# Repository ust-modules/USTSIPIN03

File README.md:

## USTSIPIN03 - Semiconductor-based ionizing radiation dosimeter and spectrometer analog front-end

The USTSIPIN03 is developed as a single-board improved variant of the [PIND02](https://github.com/mlab-modules/PIND02) and [PCRD07](https://github.com/mlab-modules/PCRD07) modules from the [MLAB.cz development system](https://www.mlab.cz/). The analog front-end is the sensing component of the [AIRDOS04 cosmic radiation detector and dosimeter](https://docs.dos.ust.cz/airdos/AIRDOS04).

### Features

* High-sensitivity silicon semiconductor PIN diode detector front-end
* Low-noise analog signal chain optimized for wide-energy radiation detection
* Designed for spectrometric and dosimetric measurements
* Suitable for connection to system MCU or FPGA via SPI interface
* Auxiliary I2C interface for service and calibration data access

### Electrical and Interface Specifications

* **Power supply**: +5 V DC
* **Maximum power consumption**: 5.5 mA (28 mW)
* **Main data interface**: SPI with up to 15 MHz system clock
* **Service interface**: I2C with access to
    * Temperature and humidity sensors
    * Unique serial number
    * Calibration memory
* Dimensions: 70.65 x 50.3 x 10 mm
* Mass: 24 g (including connector) 

### Measurement Specifications

* **Detection element**: Silicon PIN diode, volume 44 mm³
* **Effective number of energy channels**: ~65000
* **Deposited energy range**: 40 keV to 80 MeV
* **Spectral resolution**: 15 ±2 keV
* **Maximum sampling rate**: 250 kHz
* **Measurement modes**:
  * Pulse counting
  * Deposited energy spectroscopy
  * Dose rate estimation

### Applications

* Cosmic ray detection
* Environmental radiation monitoring
* Portable dosimetry systems
* Radiation protection systems
  
### Related Projects

* [AIRDOS04](https://github.com/UniversalScientificTechnologies/AIRDOS04) - Complete radiation detection system based on USTSIPIN03
* [PIND02](https://github.com/mlab-modules/PIND02) - Predecessor MLAB module
* [PCRD07](https://github.com/mlab-modules/PCRD07) - Related MLAB analog front-end module

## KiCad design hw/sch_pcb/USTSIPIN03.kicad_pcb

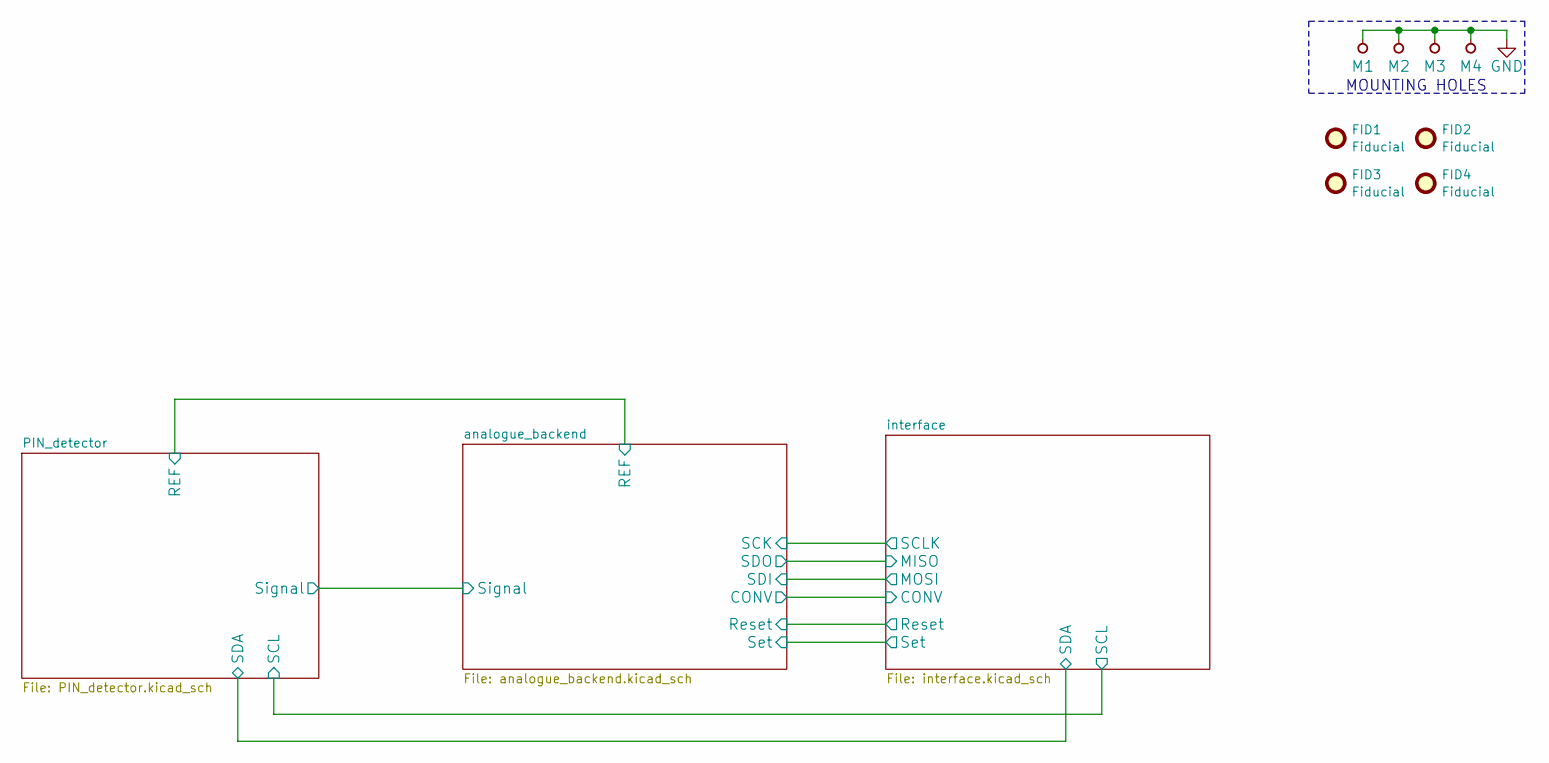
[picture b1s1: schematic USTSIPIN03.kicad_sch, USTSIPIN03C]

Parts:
FID1, FID2, FID3, FID4: Fiducial; Fiducial_1mm_Mask2mm
M1, M2, M3, M4: HOLE; MountingHole_3mm

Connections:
GND: M1.1, M2.1, M3.1, M4.1; also elsewhere on the board

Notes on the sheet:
MOUNTING HOLES

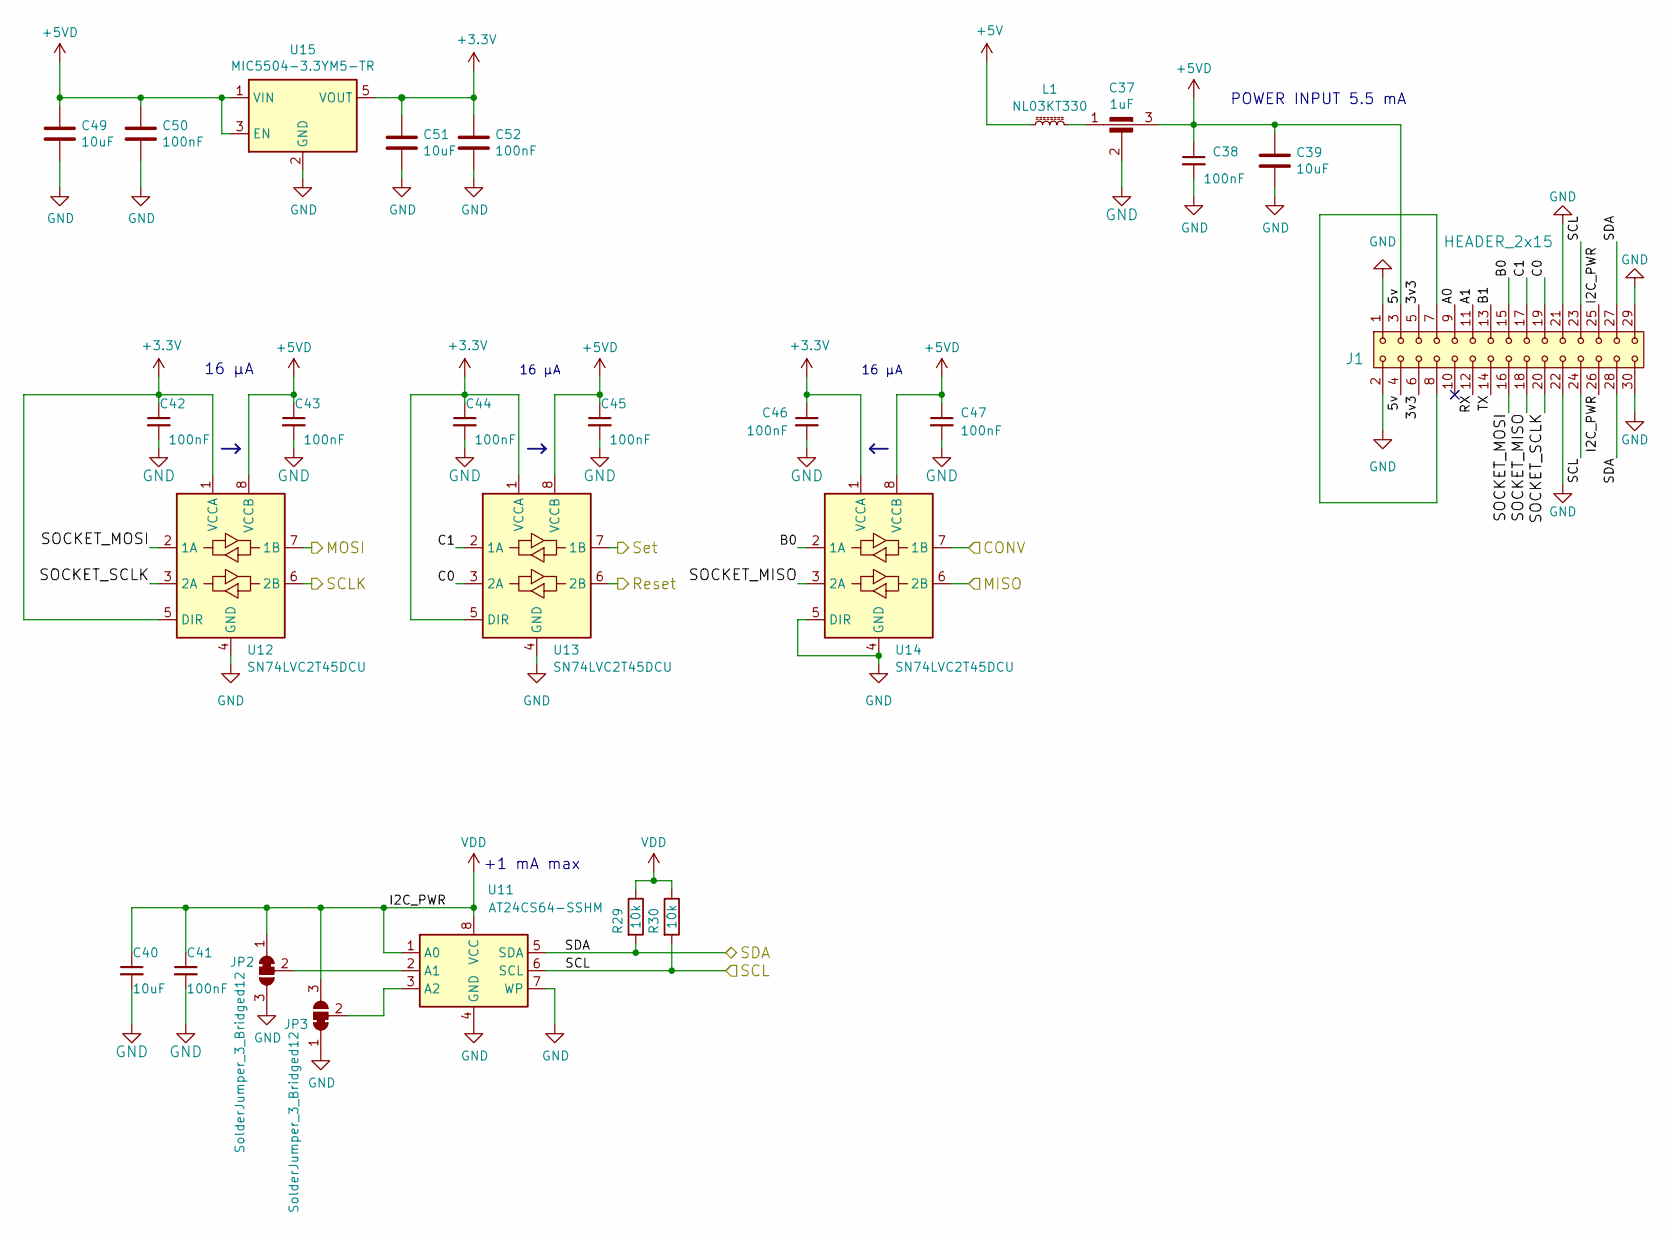
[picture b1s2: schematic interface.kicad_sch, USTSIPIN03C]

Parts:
C37: 1uF; FIR_0805
C38, C41, C42, C43, C44, C45, C46, C47, C50, C52: 100nF; C_0805_2012Metric
C39, C40, C49, C51: 10uF; C_0805_2012Metric
J1: HEADER_2x15; Straight_2x15
JP2, JP3: SolderJumper_3_Bridged12; SolderJumper-3_P1.3mm_Bridged12_RoundedPad1.0x1.5mm
L1: NL03KT330; L_0603_1608Metric_Pad1.05x0.95mm_HandSolder
R29, R30: 10k; R_0805_2012Metric
U11: AT24CS64-SSHM; SOIC-8_3.9x4.9mm_P1.27mm
U12, U13, U14: SN74LVC2T45DCU; VSSOP-8_2.3x2mm_P0.5mm
U15: MIC5504-3.3YM5-TR; SOT-23-5

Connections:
+3.3V: C42.1, C44.1, C46.1, C51.1, C52.1, U12.1 (VCCA), U12.5 (DIR), U13.1 (VCCA), U13.5 (DIR), U14.1 (VCCA), U15.5 (VOUT)
+5V: L1.1; also elsewhere on the board
+5VD: C37.3, C38.1, C39.1, C43.1, C45.1, C47.1, C49.1, C50.1, J1.3, J1.4, U12.8 (VCCB), U13.8 (VCCB), U14.8 (VCCB), U15.1 (VIN), U15.3 (EN); also elsewhere on the board
/analogue_backend/CONV: U14.7 (1B); also elsewhere on the board
/analogue_backend/Reset: U13.6 (2B); also elsewhere on the board
/analogue_backend/SCK: U12.6 (2B); also elsewhere on the board
/analogue_backend/SDI: U12.7 (1B); also elsewhere on the board
/analogue_backend/SDO: U14.6 (2B); also elsewhere on the board
/analogue_backend/Set: U13.7 (1B); also elsewhere on the board
/interface/3v3: J1.5, J1.6
/interface/A0: J1.9
/interface/A1: J1.11
/interface/B0: J1.15, U14.2 (1A)
/interface/B1: J1.13
/interface/C0: J1.19, U13.3 (2A)
/interface/C1: J1.17, U13.2 (1A)
/interface/RX: J1.12
/interface/SCL: J1.23, J1.24, R30.2, U11.6 (SCL); also elsewhere on the board
/interface/SDA: J1.27, J1.28, R29.2, U11.5 (SDA); also elsewhere on the board
/interface/SOCKET_MISO: J1.18, U14.3 (2A)
/interface/SOCKET_MOSI: J1.16, U12.2 (1A)
/interface/SOCKET_SCLK: J1.20, U12.3 (2A)
/interface/TX: J1.14
GND: C37.2, C38.2, C39.2, C40.2, C41.2, C42.2, C43.2, C44.2, C45.2, C46.2, C47.2, C49.2, C50.2, C51.2, C52.2, J1.1, J1.2, J1.21, J1.22, J1.29, J1.30, JP2.3 (B), JP3.1 (A), U11.4 (GND), U11.7 (WP), U12.4 (GND), U13.4 (GND), U14.4 (GND), U14.5 (DIR), U15.2 (GND); also elsewhere on the board
unnamed: C37.1, L1.2
unnamed: J1.7, J1.8
unnamed: JP2.2 (C), U11.2 (A1)
unnamed: JP3.2 (C), U11.3 (A2)
VDD: C40.1, C41.1, J1.25, J1.26, JP2.1 (A), JP3.3 (B), R29.1, R30.1, U11.1 (A0), U11.8 (VCC); also elsewhere on the board

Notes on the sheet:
+1 mA max
16 μA
POWER INPUT 5.5 mA

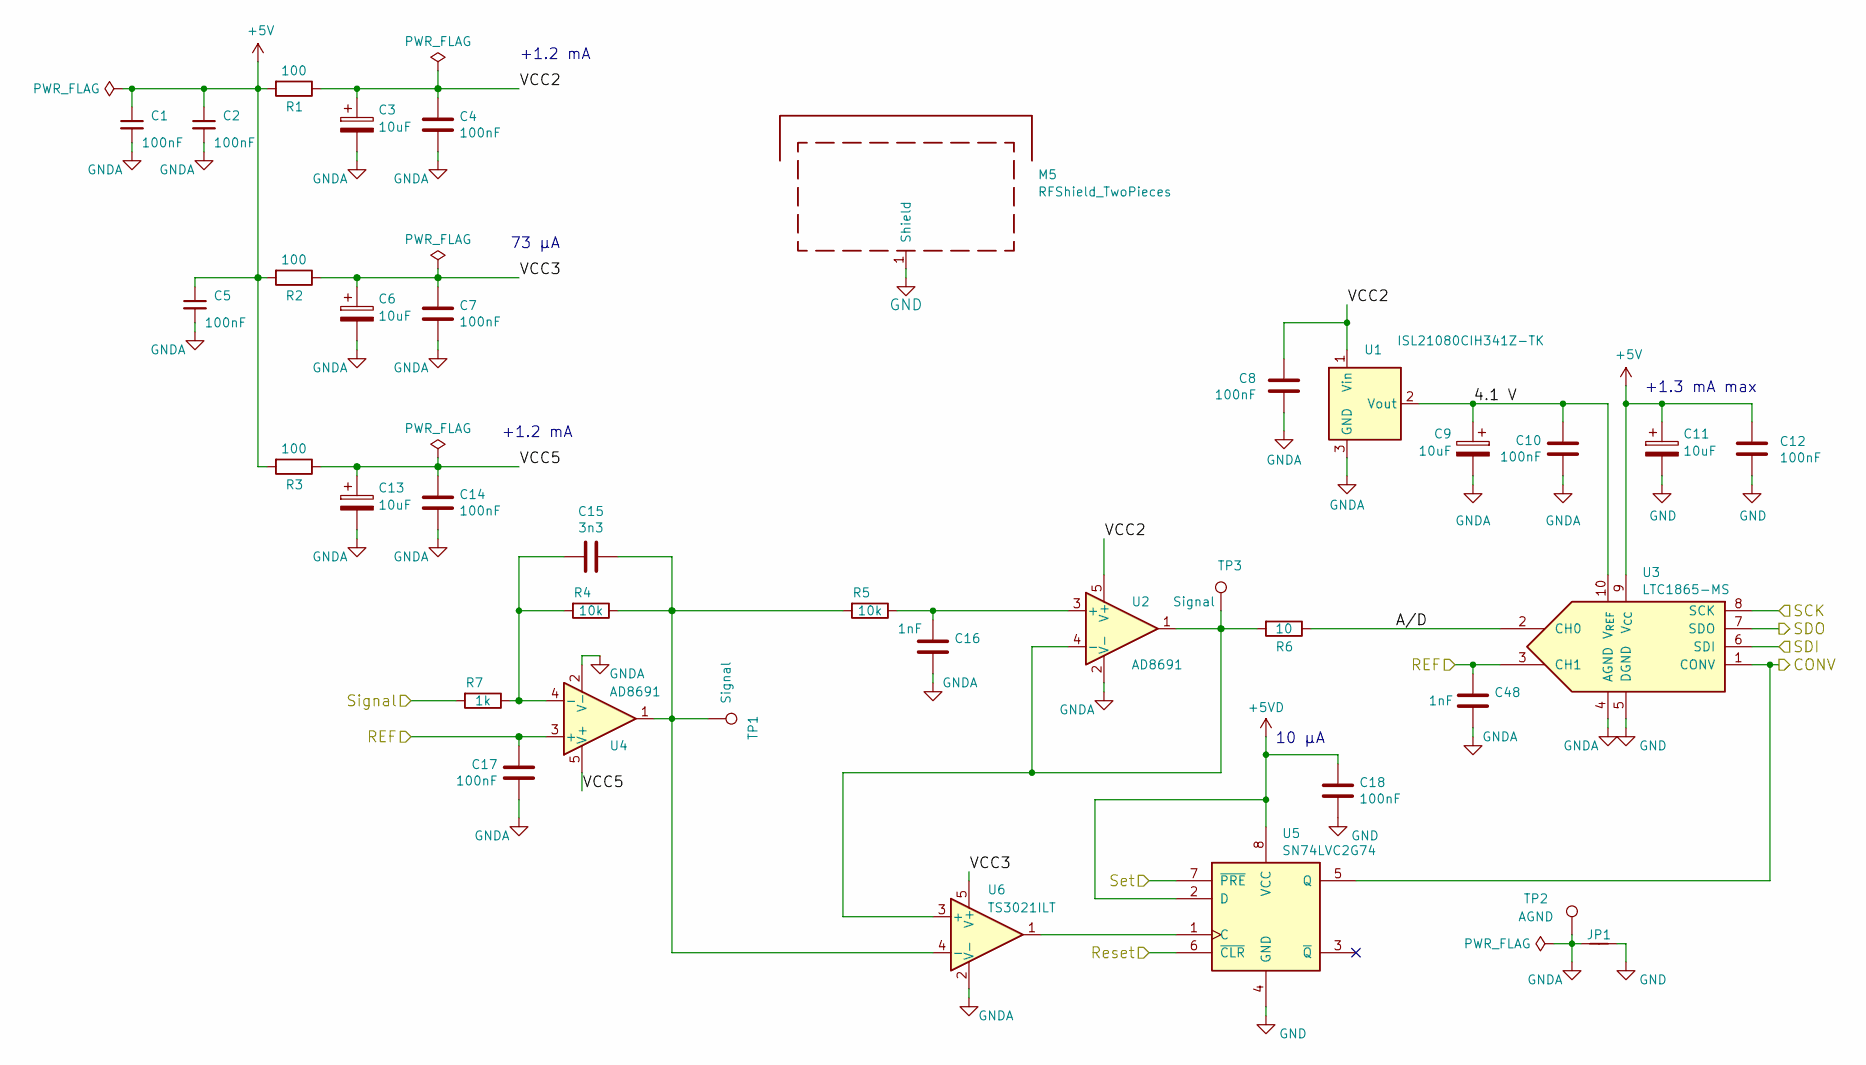
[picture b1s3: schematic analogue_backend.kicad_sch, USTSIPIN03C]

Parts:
C1, C2, C4, C5, C7, C8, C10, C12, C14, C17, C18: 100nF; C_0805_2012Metric
C3, C6, C9, C11, C13: 10uF; CP_EIA-3216-18_Kemet-A
C15: 3n3; C_0805_2012Metric
C16, C48: 1nF; C_0805_2012Metric
JP1: Jumper_2_Bridged; NetTie-2_SMD_Pad0.5mm
M5: RFShield_TwoPieces; Laird_Technologies_BMI-S-210-F_44.00x30.50mm
R1, R2, R3: 100; R_0805_2012Metric
R4, R5: 10k; R_0805_2012Metric
R6: 10; R_0805_2012Metric
R7: 1k; R_0805_2012Metric
TP1, TP3: Signal; TestPoint_Pad_D1.0mm
TP2: AGND; TestPoint_Pad_D1.0mm
U1: ISL21080CIH341Z-TK; SOT-23
U2, U4: AD8691; TSOT-23-5
U3: LTC1865-MS; MSOP-10_3x3mm_P0.5mm
U5: SN74LVC2G74; VSSOP-8_2.3x2mm_P0.5mm
U6: TS3021ILT; SOT-23-5

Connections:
+5V: C1.1, C2.1, C5.1, C11.1, C12.1, R1.2, R2.2, R3.2, U3.9 (V_{CC}); also elsewhere on the board
+5VD: C18.1, U5.2 (D), U5.8 (VCC); also elsewhere on the board
/PIN_detector/REF: C17.1, C48.1, U3.3 (CH1), U4.3 (+); also elsewhere on the board
/PIN_detector/Signal: R7.2; also elsewhere on the board
/analogue_backend/4.1 V: C9.1, C10.1, U1.2 (Vout), U3.10 (V_{REF})
/analogue_backend/A/D: R6.1, U3.2 (CH0)
/analogue_backend/CONV: U3.1 (CONV), U5.5 (Q); also elsewhere on the board
/analogue_backend/Reset: U5.6 (~CLR); also elsewhere on the board
/analogue_backend/SCK: U3.8 (SCK); also elsewhere on the board
/analogue_backend/SDI: U3.6 (SDI); also elsewhere on the board
/analogue_backend/SDO: U3.7 (SDO); also elsewhere on the board
/analogue_backend/Set: U5.7 (~PRE); also elsewhere on the board
/analogue_backend/VCC2: C3.1, C4.1, C8.1, R1.1, U1.1 (Vin), U2.5 (V+)
/analogue_backend/VCC3: C6.1, C7.1, R2.1, U6.5 (V+)
/analogue_backend/VCC5: C13.1, C14.1, R3.1, U4.5 (V+)
GND: C11.2, C12.2, C18.2, JP1.2, M5.1 (Shield), U3.5 (DGND), U5.4 (GND); also elsewhere on the board
GNDA: C1.2, C2.2, C3.2, C4.2, C5.2, C6.2, C7.2, C8.2, C9.2, C10.2, C13.2, C14.2, C16.2, C17.2, C48.2, JP1.1, TP2.1, U1.3 (GND), U2.2 (V-), U3.4 (AGND), U4.2 (V-), U6.2 (V-); also elsewhere on the board
unnamed: C16.1, R5.1, U2.3 (+)
unnamed: R6.2, TP3.1, U2.1, U2.4 (-), U6.3 (+)
unnamed: C15.2, R4.2, R7.1, U4.4 (-)
unnamed: U5.1 (C), U6.1
unnamed: C15.1, R4.1, R5.2, TP1.1, U4.1, U6.4 (-)

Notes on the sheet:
+1.3 mA max
+1.2 mA
73 μA
10 μA

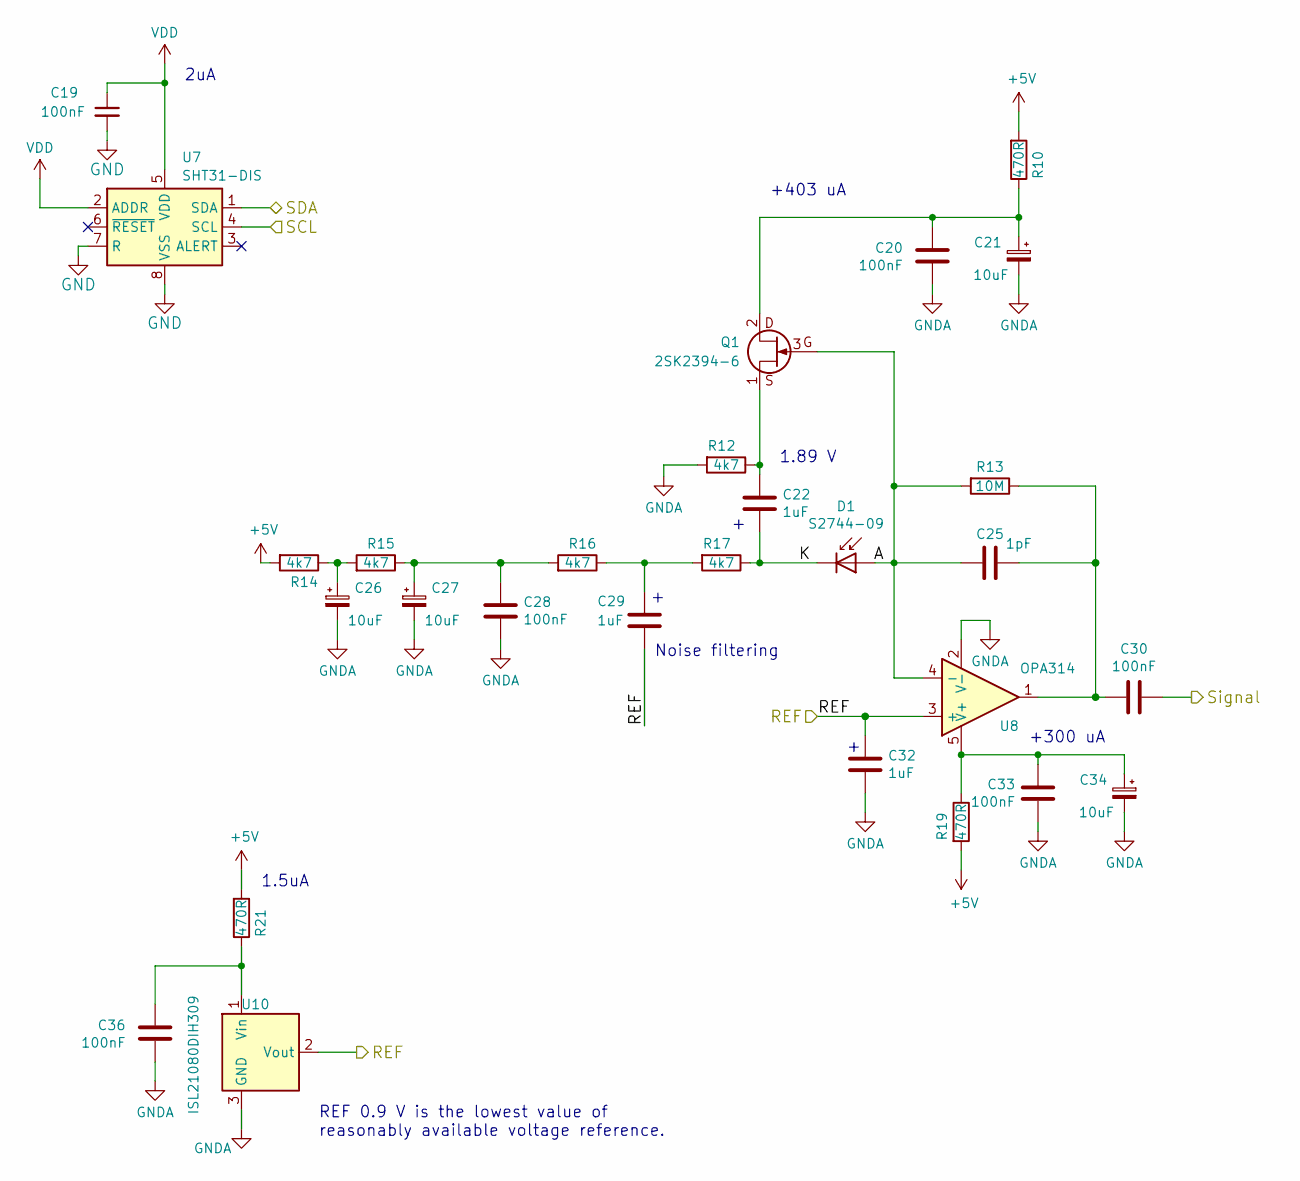
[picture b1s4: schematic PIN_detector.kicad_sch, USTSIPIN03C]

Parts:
C19, C20, C28, C30, C33, C36: 100nF; C_0805_2012Metric
C21, C26, C27, C34: 10uF; CP_EIA-3216-18_Kemet-A
C22, C29, C32: 1uF; C_1210_3225Metric
C25: 1pF; C_0805_2012Metric
D1: S2744-09; HAMAMATSU_S2744-09
Q1: 2SK2394-6; SOT-23
R10, R19, R21: 470R; R_0805_2012Metric
R12, R14, R15, R16, R17: 4k7; R_0805_2012Metric
R13: 10M; R_0805_2012Metric
U7: SHT31-DIS; Sensirion_DFN-8-1EP_2.5x2.5mm_P0.5mm_EP1.1x1.7mm
U8: OPA314; SOT-23-5
U10: ISL21080DIH309; SOT-23

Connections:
+5V: R10.2, R14.2, R19.2, R21.2; also elsewhere on the board
/PIN_detector/A: C25.2, D1.2 (A), Q1.3 (G), R13.2, U8.4 (-)
/PIN_detector/K: C22.2, D1.1 (K), R17.1
/PIN_detector/REF: C29.2, C32.1, U8.3 (+), U10.2 (Vout); also elsewhere on the board
/PIN_detector/Signal: C30.1; also elsewhere on the board
/interface/SCL: U7.4 (SCL); also elsewhere on the board
/interface/SDA: U7.1 (SDA); also elsewhere on the board
GND: C19.2, U7.7 (R), U7.8 (VSS), U7.9 (VSS); also elsewhere on the board
GNDA: C20.2, C21.2, C26.2, C27.2, C28.2, C32.2, C33.2, C34.2, C36.2, R12.2, U8.2 (V-), U10.3 (GND); also elsewhere on the board
unnamed: C25.1, C30.2, R13.1, U8.1
unnamed: C26.1, R14.1, R15.2
unnamed: C27.1, C28.1, R15.1, R16.2
unnamed: C29.1, R16.1, R17.2
unnamed: C20.1, C21.1, Q1.2 (D), R10.1
unnamed: C22.1, Q1.1 (S), R12.1
unnamed: C33.1, C34.1, R19.1, U8.5 (V+)
unnamed: C36.1, R21.1, U10.1 (Vin)
VDD: C19.1, U7.2 (ADDR), U7.5 (VDD); also elsewhere on the board

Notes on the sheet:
1.89 V
2uA
Noise filtering
REF 0.9 V is the lowest value of reasonably available voltage reference.
1.5uA
+300 uA
+403 uA

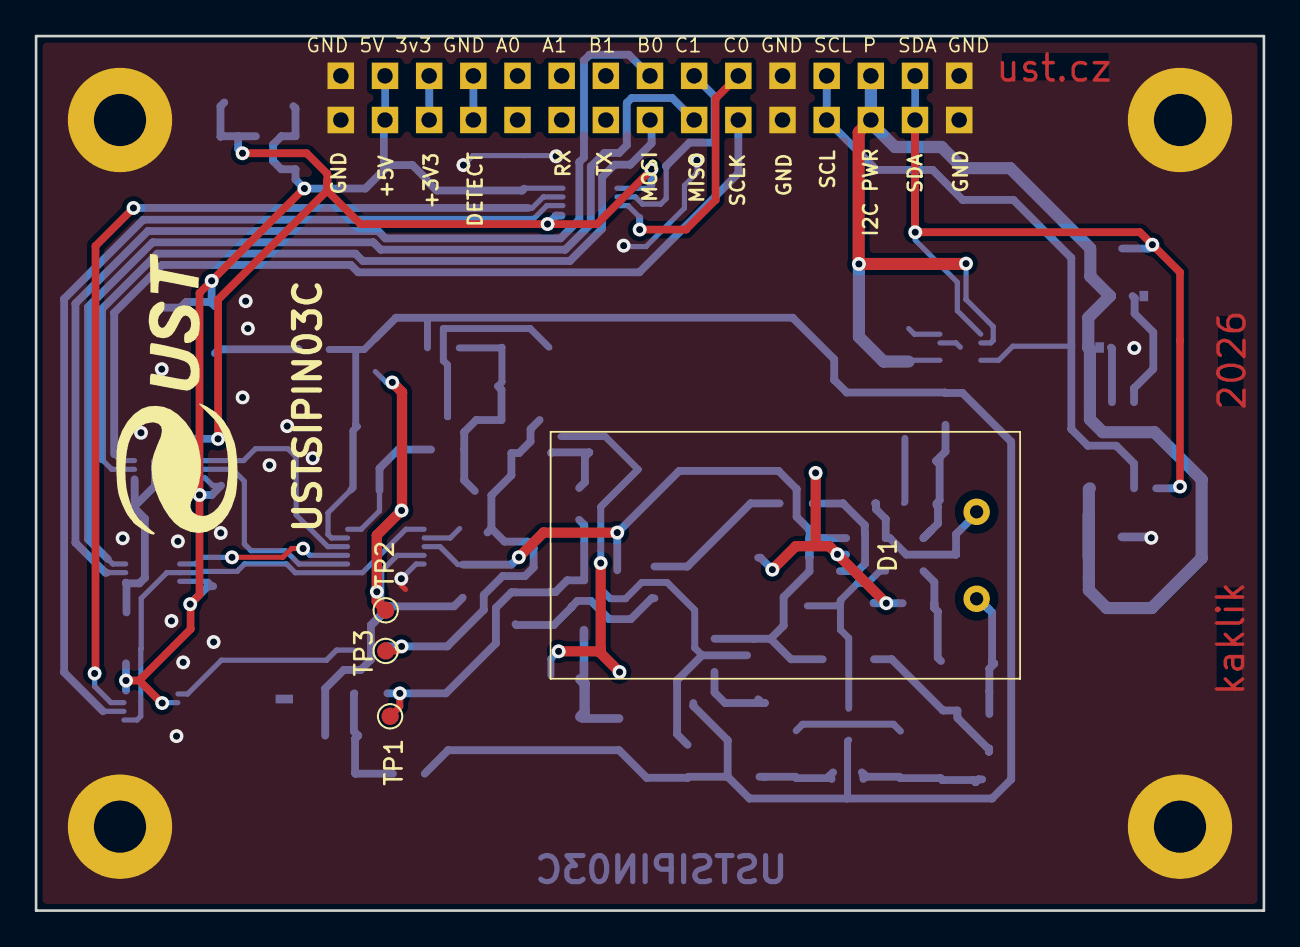
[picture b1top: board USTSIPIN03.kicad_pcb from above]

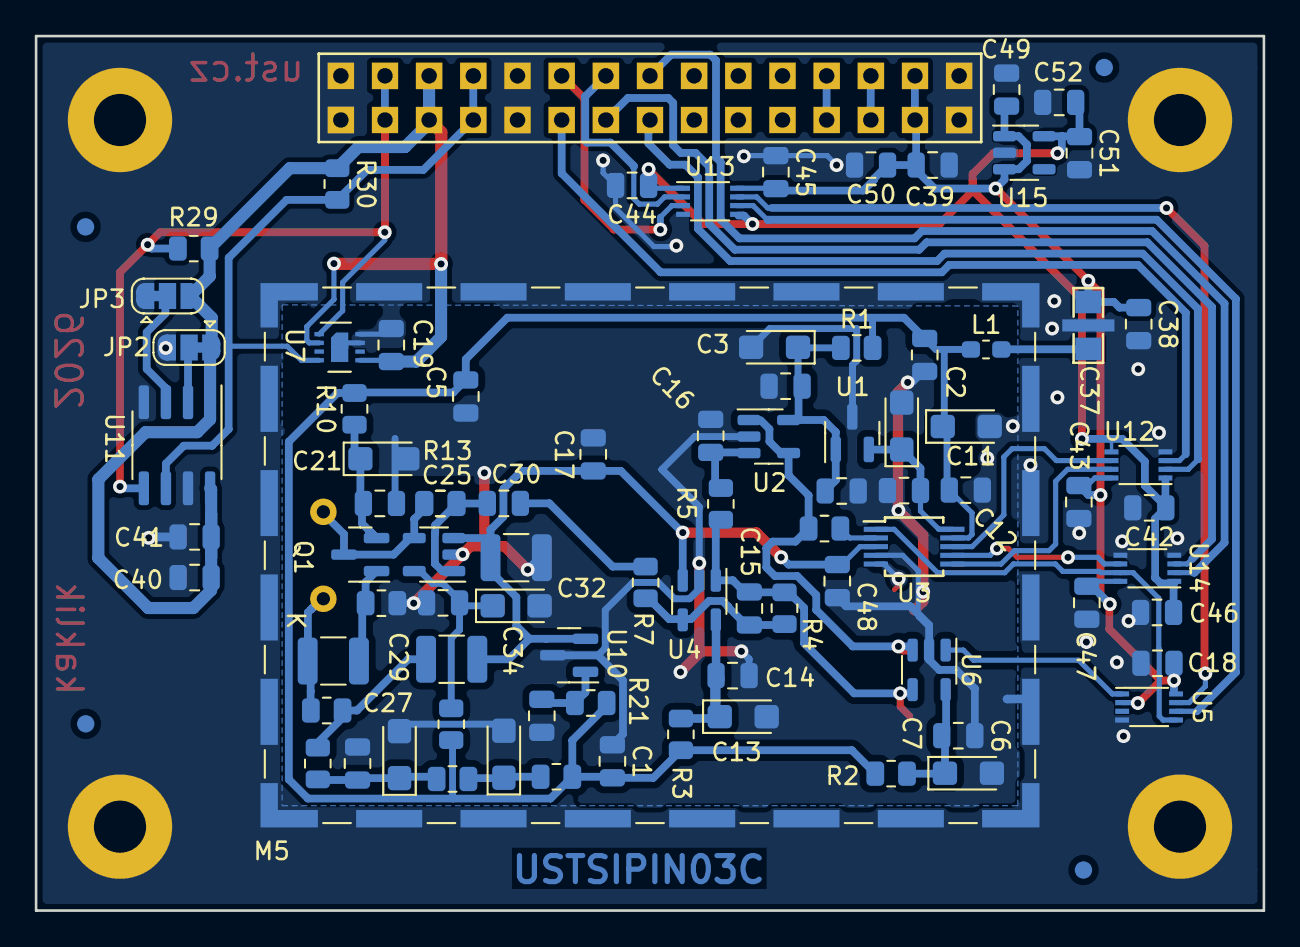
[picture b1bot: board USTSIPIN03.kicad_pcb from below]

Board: 2 copper layers, 70.6 x 50.3 mm, 100 parts (91 on the bottom side), 47 nets.

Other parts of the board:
G1: LOGO; UST

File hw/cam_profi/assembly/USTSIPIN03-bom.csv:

Row,Description,Part,References,Value,Footprint,Quantity Per PCB,Status,Datasheet,UST_ID,UST_ID2
1,,C,C25,1pF,C_0805_2012Metric,1, ,~,5c70984712875079b91f8b9f,
2,,C,C16 C48,1nF,C_0805_2012Metric,2, ,~,5c70984812875079b91f8ba6,
3,,C,C15,3n3,C_0805_2012Metric,1, ,~,651abc26462c6d9e720551fa,
4,,C_Small,C1 C2 C4 C5 C7 C8 C10 C12 C14 C17 C18 C19 C20 C28 C30 C33 C36 C38 C41 C42 C43 C44 C45 C46 C47 C50 C52,100nF,C_0805_2012Metric,27, ,~,5c70984712875079b91f8b4c 6508260b462c6d9e720541f1,
5,,C,C22 C29 C32,1uF,C_1210_3225Metric,3, ,,65082f52462c6d9e72054238,
6,,Filter_EMI_C,C37,1uF,FIR_0805,1, ,http://www.murata.com/~/media/webrenewal/support/library/cat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,5c70984412875079b91f880f,
7,,C_Polarized,C3 C6 C9 C11 C13,10uF,CP_EIA-3216-18_Kemet-A,5, ,~,65089dd0462c6d9e720542b3,
8,,C_Polarized_Small,C21 C26 C27 C34,10uF,CP_EIA-3216-18_Kemet-A,4, ,https://eu.mouser.com/datasheet/2/40/TAJ-3165264.pdf,65089dd0462c6d9e720542b3,
9,,C,C39 C40 C49 C51,10uF,C_0805_2012Metric,4, ,~,5c70984712875079b91f8b53,
10,,D_Photo,D1,S2744-09,HAMAMATSU_S2744-09,1, ,https://www.hamamatsu.com/content/dam/hamamatsu-photonics/si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,628d118cdc56076e9a2235e4,
11,,LOGO,G1,LOGO,UST,1, ,~,,
12,,HEADER_2x15,J1,HEADER_2x15,Straight_2x15,1, ,,,
13,,L_Ferrite_Small,L1,NL03KT330,L_0603_1608Metric_Pad1.05x0.95mm_HandSolder,1, ,~,64fe1808f3b9d36f37fc944d,
14,,HOLE,M1 M2 M3 M4,HOLE,MountingHole_3mm,4, ,,,
15,,RFShield_TwoPieces,M5,RFShield_TwoPieces,Laird_Technologies_BMI-S-210-F_44.00x30.50mm,1, ,~,5c70984312875079b91f873d,5c70984312875079b91f873c
16,,Q_NJFET_SDG,Q1,2SK2394-6,SOT-23,1, ,~,628d134fdc56076e9a223625,
17,,R,R6,10,R_0805_2012Metric,1, ,~,5c70984512875079b91f896d,
18,,R,R1 R2 R3,100,R_0805_2012Metric,3, ,~,5c70984512875079b91f8977,
19,,R,R10 R19 R21,470R,R_0805_2012Metric,3, ,~,5c70984512875079b91f8986,
20,,R,R7,1k,R_0805_2012Metric,1, ,~,5c70984512875079b91f898c,
21,,R,R12 R14 R15 R16 R17,4k7,R_0805_2012Metric,5, ,~,5c70984612875079b91f8995,
22,,R,R4 R5 R29 R30,10k,R_0805_2012Metric,4, ,~,5c70984612875079b91f899f,
23,,R,R13,10M,R_0805_2012Metric,1, ,~,5c70984712875079b91f8aae,
24,,AD8691,U2 U4,AD8691,TSOT-23-5,2, ,https://www.analog.com/media/en/technical-documentation/data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,5d47c084128750448e6b4671,
25,,AT24CS64-SSHM,U11,AT24CS64-SSHM,SOIC-8_3.9x4.9mm_P1.27mm,1, ,http://ww1.microchip.com/downloads/en/DeviceDoc/Atmel-8870-S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,5c70984712875079b91f8b99,
26,,ISL21070CIH320Z-TK,U1,ISL21080CIH341Z-TK,SOT-23,1, ,https://cz.mouser.com/datasheet/2/698/REN_isl21080_DST_20040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,6555591d0c8d609e3e79abc1,
27,,ISL21070CIH320Z-TK,U10,ISL21080DIH309,SOT-23,1, ,https://www.renesas.com/us/en/document/dst/isl21080-datasheet,5c70984712875079b91f8b0b,
28,,LTC1865-MS,U3,LTC1865-MS,MSOP-10_3x3mm_P0.5mm,1, ,https://www.analog.com/media/en/technical-documentation/data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,67f14385ee7fc534862c535e,
29,,MIC5504-3.3YM5,U15,MIC5504-3.3YM5-TR,SOT-23-5,1, ,http://ww1.microchip.com/downloads/en/DeviceDoc/MIC550X.pdf,5c7255e81287500b4e112ea2,
30,,OPA314,U8,OPA314,SOT-23-5,1, ,https://www.ti.com/lit/ds/symlink/opa314.pdf,5c70984412875079b91f879a,
31,,SHT31-DIS,U7,SHT31-DIS,Sensirion_DFN-8-1EP_2.5x2.5mm_P0.5mm_EP1.1x1.7mm,1, ,https://sensirion.com/media/documents/213E6A3B/63A5A569/Data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,5c70984612875079b91f89e4,
32,,74LVC2G74,U5,SN74LVC2G74,VSSOP-8_2.3x2mm_P0.5mm,1, ,https://www.ti.com/lit/ds/symlink/sn74lvc2g74-ep.pdf,65555d4795a79cc5ac409b41,
33,,74LVC2T45DC,U12 U13 U14,SN74LVC2T45DCU,VSSOP-8_2.3x2mm_P0.5mm,3, ,https://assets.nexperia.com/documents/data-sheet/74LVC_LVCH2T45.pdf,65555a850c8d609e3e79abde,
34,,AD8691,U6,TS3021ILT,SOT-23-5,1, ,https://www.st.com/resource/en/datasheet/ts3021.pdf,5d47bfd4128750448e6b465e,





Project info:
Schematic:,USTSIPIN03
Variant:,default
Revision:,
Date:,2024-05-30
KiCad Version:,8.0.8+1
Statistics:
Component Groups:,34
Component Count:,90
Fitted Components:,90
Number of PCBs:,1
Total Components:,90

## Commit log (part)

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2025-02-15 Update project to KiCADv8.
2025-02-15 Update actions products
2025-02-15 Fix #8 Adding solder jumpers.
2025-02-16 Resolve #10
2025-02-16 Improve layout.
2025-03-02 Cleanup Fab layer.
2025-04-26 Fix wrong revision in silkscreen.
2025-05-05 Update UST_ID for ADC.
2025-08-18 Update workflow files
2026-01-16 Update KiCAD project.
2026-01-21 Add dimensioned drawing.
2026-03-06 Add modified version of sensor frame.

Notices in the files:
hw/sch_pcb/USTSIPIN03.kicad_sch:
GPL 3
